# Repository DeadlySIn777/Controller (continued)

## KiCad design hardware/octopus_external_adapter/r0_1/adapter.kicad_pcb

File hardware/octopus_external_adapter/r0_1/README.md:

# Octopus external-driver adapter r0.1

**Engineering candidate for review and PCBWay DFM. Do not build or order from this revision yet.**

This is a separate single-axis StepStick adapter with a keyed four-pin output and a matching factory-made cable. The quote scenario is five assembled adapters and five cables: four axes plus one spare. Quantity and the proposed 500 mm cable length remain provisional.

**Confirmed delivery requirement: full turnkey assembly.** PCBWay is to fabricate the boards, source and fit all 12 components including every connector, manufacture and finish the matching cables, complete the agreed inspections/tests, and deliver depanelled, individually ESD-packed sets. The user receives finished assemblies requiring no soldering or crimping. Installation consists of plugging in each adapter/cable and securing the labelled leads in the driver terminals. This requirement does not change the unresolved compatibility or release gates.

The selected connector pair is a top-mounted JST `B4B-XH-A(LF)(SN)` shrouded header and cable `XHP-4` housing with female contacts. It provides the plug-in connection requested; the PCB header's protected contacts are male. Matching cables will be supplied, so the pictured cable is not assumed compatible.

| J3 cavity | Signal | Driver end |
| --- | --- | --- |
| 1 | +5 V common | Factory splice to PUL+, DIR+, ENA+ |
| 2 | PUL- | PUL- |
| 3 | DIR- | DIR- |
| 4 | ENA- | ENA- |

The candidate uses socket 5 V and an `SN74LVC3G06DCUR` triple open-drain inverter. **The VM contact and plated hole are physically absent**: J1 is an eight-pin header; J2 is a seven-pin header beginning one position lower, at GND. It is based on the **Octopus Pro V1.0 F429/F446** schematic, whose socket control signals are already buffered to 5 V. The user's exact board is unconfirmed. This is not a general 3.3 V-input adapter. The **CL57T V4.1** driver comes from the pasted discussion and also remains unconfirmed.

The **15.24 × 20.32 mm, two-layer** PCB is routed. Final native KiCad 10.0.4 ERC and DRC each report **zero errors and zero warnings**, with **zero unconnected items, zero schematic discrepancies and zero ignored checks**. The independent package check reconciles all **43 pin assignments, 12 components, 11 functional nets**, both header positions and nine SMT placements. Two filled ground copper layers connect the buffer and bypass returns. These are source/CAD results, not measured hardware performance; exact hashes and outstanding gates are in [verification.json](verification.json).

Start with the [actual 3D CAD render](adapter-3d.png), [assembly drawing](assembly-review.svg), [schematic PDF](adapter-schematic.pdf), or editable [PCB](adapter.kicad_pcb) and [schematic](adapter.kicad_sch). The [STEP assembly](adapter-assembly-review.step) supports mechanical review. The [PCBWay BOM](PCBWay_BOM_DRAFT.csv), [SMT placement file](PCBWay_CPL_DRAFT.csv), [quote draft](PCBWAY_QUOTE_DRAFT.md), [harness specification](HARNESS_SPEC.md), [cable pin map](cable_pinmap.csv), [cable BOM](cable_bom.csv), [test plan](FUNCTIONAL_TEST.md), and [sources](SOURCES.md) prepare the review package. All ordering files remain drafts. CPL origin is the lower-left board corner, X right/Y up, millimetres; THT assembly is specified separately.

Prototype order release still needs the exact host and driver identities, socket supply/logic confirmation, populated mechanical fit, driver-terminal/ferrule details, enable polarity and host timing review, and factory DFM/quotation. Quantity and cable length are provisional. The native source/PCB reconciliation is complete for this candidate. Before machine use, a first article requires loaded electrical, pulse, enable, power-sequence and actual-cable tests. The adapter makes no emergency-stop, STO or power-loss inhibition claim; alarm/brake/motor/encoder wiring remains separate.

Gerbers/drills have deliberately not been exported from this unreleased equipment profile. No external submission, quotation, purchase or physical test has occurred. The active twelve-channel controller motherboard, its routing, machine configurations and historical evidence were not edited for this adapter.

The reproducible sources are `build_schematic.py`, `build_pcb.py`, `route_candidate.py` and `package_review.py`. Use KiCad's bundled Python for the PCB scripts. `build_pcb.py` applies saved `routes.json`; changing placement or circuit requires rerouting and fresh native checks. After building, run native DRC with `--refill-zones --save-board --schematic-parity --severity-all`, and native ERC with `--severity-all`. Keep all release gates open until their evidence exists.

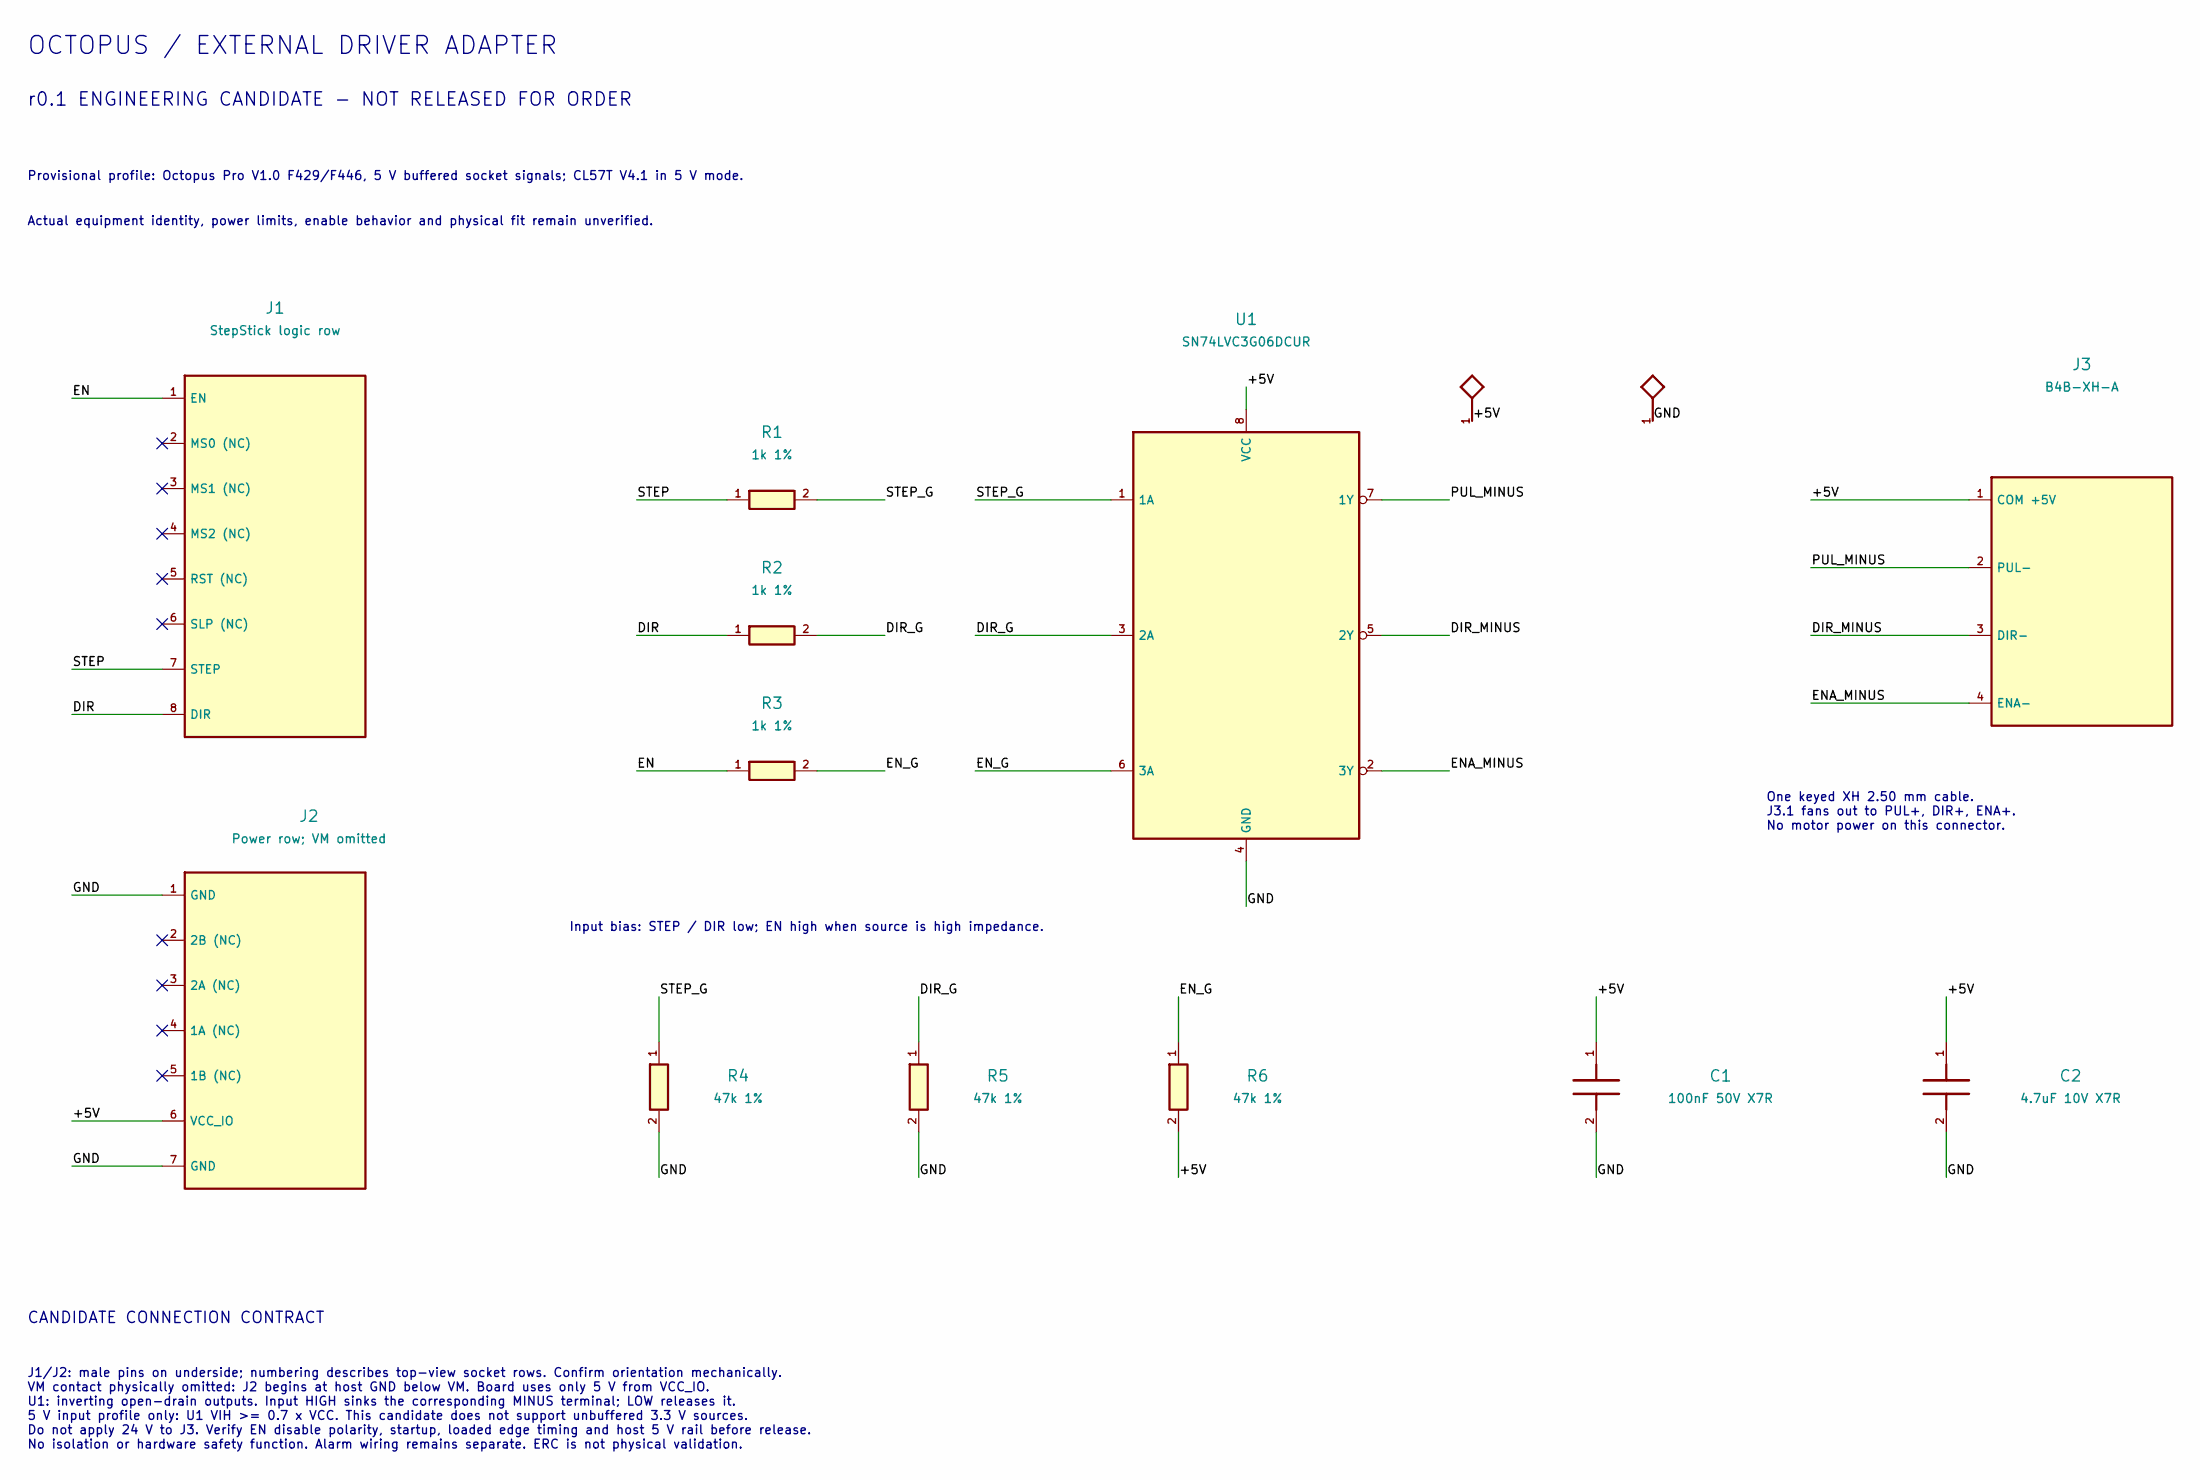
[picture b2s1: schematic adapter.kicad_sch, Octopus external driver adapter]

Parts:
C1: 100nF 50V X7R; C_0603_1608Metric; MPN CL10B104KB8NNNC
C2: 4.7uF 10V X7R; C_0805_2012Metric; MPN CC0805KKX7R6BB475
J1: StepStick logic row; Wurth_61300811121_1x08_P2.54mm; MPN 61300811121
J2: Power row; VM omitted; Wurth_61300711121_1x07_P2.54mm; MPN 61300711121
J3: B4B-XH-A; JST_XH_B4B-XH-A_1x04_P2.50mm_Vertical; MPN B4B-XH-A(LF)(SN)
R1, R2, R3: 1k 1%; R_0603_1608Metric; MPN RC0603FR-071KL
R4, R5, R6: 47k 1%; R_0603_1608Metric; MPN RC0603FR-0747KL
U1: SN74LVC3G06DCUR; VSSOP-8_2.3x2mm_P0.5mm; MPN SN74LVC3G06DCUR

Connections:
/+5V: C1.1, C2.1, J2.6 (VCC_IO), J3.1 (COM +5V), R6.2, U1.8 (VCC)
/DIR: J1.8 (DIR), R2.1
/DIR_G: R2.2, R5.1, U1.3 (2A)
/DIR_MINUS: J3.3 (DIR-), U1.5 (2Y)
/EN: J1.1 (EN), R3.1
/ENA_MINUS: J3.4 (ENA-), U1.2 (3Y)
/EN_G: R3.2, R6.1, U1.6 (3A)
/GND: C1.2, C2.2, J2.1 (GND), J2.7 (GND), R4.2, R5.2, U1.4 (GND)
/PUL_MINUS: J3.2 (PUL-), U1.7 (1Y)
/STEP: J1.7 (STEP), R1.1
/STEP_G: R1.2, R4.1, U1.1 (1A)

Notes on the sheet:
OCTOPUS / EXTERNAL DRIVER ADAPTER
r0.1 ENGINEERING CANDIDATE - NOT RELEASED FOR ORDER
Provisional profile: Octopus Pro V1.0 F429/F446, 5 V buffered socket signals; CL57T V4.1 in 5 V mode.
Actual equipment identity, power limits, enable behavior and physical fit remain unverified.
One keyed XH 2.50 mm cable. J3.1 fans out to PUL+, DIR+, ENA+. No motor power on this connector.
Input bias: STEP / DIR low; EN high when source is high impedance.
CANDIDATE CONNECTION CONTRACT
J1/J2: male pins on underside; numbering describes top-view socket rows. Confirm orientation mechanically. VM contact physically omitted: J2 begins at host GND below VM. Board uses only 5 V from VCC_IO. U1: inverting open-drain outputs. Input HIGH sinks the corresponding MINUS terminal; LOW release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

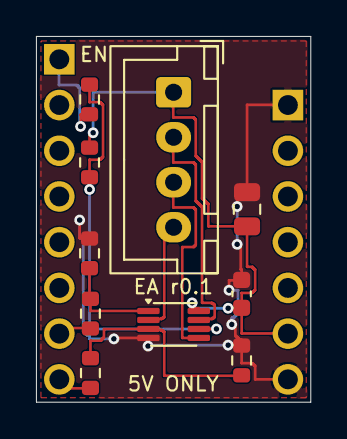
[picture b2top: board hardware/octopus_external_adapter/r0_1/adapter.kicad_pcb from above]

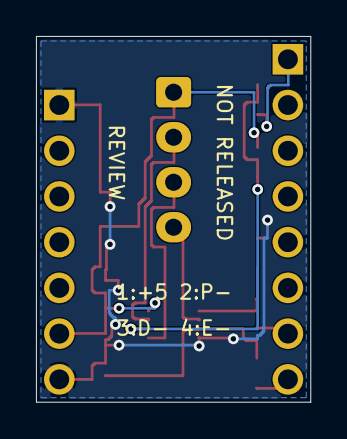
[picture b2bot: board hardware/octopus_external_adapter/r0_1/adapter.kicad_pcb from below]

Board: 2 copper layers, 15.2 x 20.3 mm, 12 parts (2 on the bottom side), 11 nets.

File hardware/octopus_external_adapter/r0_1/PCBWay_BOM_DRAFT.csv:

Designator,Quantity per board,Value,Manufacturer,MPN,Footprint,Assembly side,Type,Assembly note
J1,1,StepStick logic row,Wurth Elektronik,61300811121,Adapter:Wurth_61300811121_1x08_P2.54mm,Bottom,THT,Long mating pins point DOWN; VM position omitted on right row
J2,1,Power row; VM omitted,Wurth Elektronik,61300711121,Adapter:Wurth_61300711121_1x07_P2.54mm,Bottom,THT,Long mating pins point DOWN; VM position omitted on right row
J3,1,B4B-XH-A,JST,B4B-XH-A(LF)(SN),Connector_JST:JST_XH_B4B-XH-A_1x04_P2.50mm_Vertical,Top,THT,Cable entry UP
U1,1,SN74LVC3G06DCUR,Texas Instruments,SN74LVC3G06DCUR,Package_SO:VSSOP-8_2.3x2mm_P0.5mm,Top,SMT,
R1,1,1k 1%,Yageo,RC0603FR-071KL,Resistor_SMD:R_0603_1608Metric,Top,SMT,
R2,1,1k 1%,Yageo,RC0603FR-071KL,Resistor_SMD:R_0603_1608Metric,Top,SMT,
R3,1,1k 1%,Yageo,RC0603FR-071KL,Resistor_SMD:R_0603_1608Metric,Top,SMT,
R4,1,47k 1%,Yageo,RC0603FR-0747KL,Resistor_SMD:R_0603_1608Metric,Top,SMT,
R5,1,47k 1%,Yageo,RC0603FR-0747KL,Resistor_SMD:R_0603_1608Metric,Top,SMT,
R6,1,47k 1%,Yageo,RC0603FR-0747KL,Resistor_SMD:R_0603_1608Metric,Top,SMT,
C1,1,100nF 50V X7R,Samsung Electro-Mechanics,CL10B104KB8NNNC,Capacitor_SMD:C_0603_1608Metric,Top,SMT,
C2,1,4.7uF 10V X7R,Yageo,CC0805KKX7R6BB475,Capacitor_SMD:C_0805_2012Metric,Top,SMT,

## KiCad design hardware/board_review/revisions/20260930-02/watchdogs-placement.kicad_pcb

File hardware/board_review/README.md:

# Live board CAD review

**Current adopted board — Source26/ROOT104, published CAD30:** [Exact adoption](../../reports/motherboard-return-zoning-20261002/ROOT103-bypass-PROC-composed-r01/adoption.json) and the published board share SHA-256 `70b71c36778e49600b77f382cf84df81ef3ac6dce442cc0e576b494d307979cc`. There are **2,688 footprints, 11,807 track/via items, 1,544 zones/rule areas and 3,508 required joins remaining**. Native and independent uncapped connectivity agree: 633 fully joined and 1,101 incomplete multi-pad nets, zero orphan copper. Native regular DRC is **0 errors/0 warnings/no ignored checks**; Source26 ERC is **0 errors/70 unsuppressed warnings**, with [exact warning dispositions](../../reports/motherboard-erc-20261002/source26-exact-warning-disposition-r01/receipt.json). The 48 controlled additions preserve all prior copper, lands, poses and zone definitions. Actual saved/refilled removal of all 48 restores the baseline 3521 joins. Scoped proofs cover 120 bypass loops, 245 receiving returns and 188 Source-anchored filled resources. Source27 corrections remain staged; no Freerouting copper has been adopted.

[Fresh full r08](../../reports/pre-hardware-validation-20261002/full-bypass-PROC-seeded-IS2-r08/report.json) has **25 PASS, 9 BLOCKED, 1 physical NOT_RUN and 0 FAIL**, with **1,895 host and 238 native KiCad cases passing**, five Windows symlink skips and all 4,041 scoped source hashes unchanged. Fresh evidence includes 2,048 actual SPI seeded trials in eight fault classes, 18 reset/fault mechanical-model scenarios, the four-stage diagnostic IOL1 replay, the five-stage read-only IS2 CAP3 profile and eleven-stage stateful replay. These are compiled C/RTL and ideal-mechanics proofs, not complete HAL, target timing, electrical safety or measured hardware ratings.

[Characterization r06](../../reports/pre-hardware-characterization-20261002/characterization-register-r06/requirements-and-coverage.json) preserves all 15 subsystem, 22 fault and nine complete-machine requirements. No complete machine profile is yet validated. The original transport CAP3 gap and the bounded IS2 read-only implementation are distinct; the new profile deliberately remains unqualified and cannot authorize motion. Frozen CNC3 rate limits remain unchanged; the requested 2 MHz/channel target is not implemented/qualified. Complete IOL1 authority, record trust/provisioning, analog-chain convergence, vendor FPGA fit/timing and full-load operation remain open. The staged record-acquisition mapping exceeds the coarse T20 resource budget and is undergoing implementation optimization; HDL simulation alone does not prove capacity.

[Current native drill/land audit](../../reports/motherboard-pcb-integration-20261002/ROOT103-bypass-PROC-full-drill-SMD-r01/receipt.json) finds **274 drilled vias intersecting 277 same-net paste SMD lands**, zero foreign-net intersections and no added overlap in ROOT104. This lower bound excludes tangency and registration margins. Layout correction or exact qualified filled/capped fabrication and assembly is still required; tenting and clean ordinary DRC do not close it. The **460×340 mm, six-layer, 1.6 mm** stackup remains provisional. Final routing, power distribution, complete 20 ms inhibit, mechanics, manufacturing outputs and physical validation are unfinished. **Manufacturing readiness remains false.**

[Unchanged Source26 partial BOM v11](../../reports/motherboard-cost-20260930/source-r26-2688-complete-cost-v11/README.md) has known-priced consumed parts at 1/10/100 units of **US$1,091.51/$877.37/$796.51**; 105 exact MPNs are priced and 185 MPNs/720 fitted pieces remain unpriced. Plug-in modules, screens, fabrication, assembly, programming/test, enclosure and packaging remain separate unknowns. This is not a complete product cost or PCBWay quote.

30 September 2026. User-requested physical design view, backed by editable native KiCad placement files. Open `http://127.0.0.1:8788/index.html` in the Codex right panel while the local review server runs. It serves only this review folder on loopback; it does not connect to a machine or require an online service.

The viewer offers top CAD, native KiCad 3D renders, pan/zoom, component search, source part and pin-net inspection, highlighted changes/review focus and a revision selector. It polls the published manifest every three seconds. A newly published revision updates the latest view; an intentionally selected old revision stays visible until the user selects the update. The server does **not** regenerate CAD when schematics change: the engineering update procedure below publishes that change.

## Current published revision: 20261002-30; working PCB: Source26/ROOT104

[Native KiCad project](revisions/20261002-30/motherboard-native-candidate.kicad_pcb), [native render](revisions/20261002-30/motherboard-3d.png) and [publication proof](revisions/20261002-30/publication.json) share the adopted board bytes. Publication reruns native DRC and uncapped connectivity; the 499-item native display cap is not the 3508 required-join total. The package retains92 checked footprint patterns and both local model references. This is an incomplete editable design, not a fabrication package.

## Historical published revision: 20260930-21

Published native CAD **20260930-21** contains the separate frozen **880-footprint / 878 fitted** snapshot. It preserves the original 327 footprints, **2,088 track/via items and five filled zones**. Independent uncapped connectivity finds **1,600 missing joins**. Native DRC reports **zero regular violations, no ignored checks and 499 capped unconnected items**; routing fails. The **460 × 340 mm, six-layer, 1.6 mm** outline remains provisional; existing planes cover the retained core rather than the whole motherboard.

The reconciled electrical source has **1585 physical footprints: 1557 purchased fitted parts, 26 bare PCB test pads and two DNP footprints**, across eighteen source blocks. It contains all twelve motor interfaces, four ABZ receiving paths, 24 DI, 16 smart DO, power-health, actual I/O controllers, protected power entry, probe/pendant supplies, purchased-module compute/ESP sockets and process control with its fourth actual acquisition controller. Native integrated ERC is **zero errors, 72 warnings, no ignored checks** (70 isolated-pin labels and two ground-name warnings). Independent native fitted pin/MPN/footprint and exact original-pin/topology checks pass. The 23 root integration, 26 FPGA allocation, 33 ACC, 35 process and 10 ESP focused tests pass; these do not prove firmware execution or physical behavior.

The additional source parts are being populated onto the existing PCB without discarding its routed copper. Storage and compute raw peripherals, analog/comms, status indicators, actual field terminals, complete power/return routing and mechanical/thermal reconciliation remain engineering work. Logic-rail startup load and monitor-window corrections are under review. The 20 ms inhibit requirement, partial-power behavior, target firmware, vendor FPGA package fit/timing and physical/EMC/thermal qualification remain unproved. Gerbers, drills, final assembly CPL/drawings and a final stackup have not been released; manufacturing_ready remains false. Original six-joint/two-encoder runtime results remain historical baseline evidence; twelve fitted interfaces are not twelve proven coordinated axes.

[Native PCB](revisions/20260930-21/motherboard-populated-candidate.kicad_pcb), [publication receipt](revisions/20260930-21/publication.json), [uncapped connectivity](revisions/20260930-21/publication-connectivity/review.json).

## Historical initial CAD scope: revisions 01â€“03

The following table and observations describe the initial placement studies, not the current integrated MC. Their original native files, source review and DRC records remain historical evidence. Later integration and partial routing are recorded above.

| Study | Current physical review content | Important boundary |
|---|---|---|
| MC motion card | 70 FPGA-core component candidates, 411 pads, 214 represented nets | Proposed IS-1 220 Ã— 100 mm card envelope; not a complete motion card |
| Dual-watchdog circuit | 22 component candidates, 68 pads, 18 represented nets | Separate unintegrated circuit on a provisional 60 Ã— 45 mm review canvas; not an adopted product module |

MC imports 68 footprint assignments from the electrical source and makes **two placement-only** assignments for U1 and Y1. Their pad numbering/body geometry was independently checked in [the source review](../../reports/board-cad-20260930/SOURCE_REVIEW.md); their source schematic/BOM assignments remain unchanged. Logical boundary symbols are recorded but have not been turned into fabricated connectors. All fitted native-board pad nets round-trip against the source netlists. No copper tracks, planes, vias, stackup qualification, final connector placement, mounting holes or fabrication exports exist here. The study's 1.6 mm thickness is an explicit assumption.

The MC's card-local power, identity, Ioff buffering, final permission/self-test circuits and connector allocation remain incomplete. The watchdogs are not integrated into MC; their known startup and conditioning issues remain open. Other controller cards and the passive wiring base have no new board layout in this delivery. The historical six/two runtime and required eight/twelve product scope remain distinct from CAD placement evidence.

The top view shows every imported footprint. Installed 3D models cover **68/70 MC parts** and **20/22 watchdog parts**. The native 3D render omits the body models for MC U1/Y1 and watchdog U1/U2; their actual pads remain present. The viewer states these omissions explicitly rather than inventing package heights.

Native DRC ran on revision `20260930-03`: no other reported rule violations, but **197 MC and 50 watchdog unconnected items** remain. This is an **unrouted DRC result, not a DRC pass or manufacturing approval**. Schematic parity, board-level electrical completeness and physical measurements are not established by this review. Raw native reports and independent placement review are under `reports/board-cad-20260930/`.

The [independent native placement QA](../../reports/board-cad-20260930/PLACEMENT_QA.md) checks source pin sets, pad nets, manifest geometry/hashes and conservative pad/component/courtyard envelopes. It found no intersecting or outside checked envelopes. Watchdog U1/U2 have **no source courtyard shapes**, so their courtyard check remains incomplete. The native study files use KiCad's default two copper layers; that is a review-file default, **not** the selected production stackup.

## Updating the view as engineering changes

For a routed candidate, preserve the prior published native copper and compare both source-pin/net parity and actual physical connectivity before publishing. `tools/publish_routed_board_review.py` publishes a reviewed routed board under a new unique revision, with optional staged placement inputs, fresh native DRC/render and a publication receipt. The builder example below remains the placement-study workflow; rebuilding placement alone is not a substitute for preserving and verifying existing routed geometry. Do not report the capped native unconnected list as an uncapped routing total. Keep the independent all-net inventory synchronized with the actual published board hash.

1. Update the electrical circuit through its existing generator/review workflow, preserving the user sources and machine configurations.
2. Update `placement.json` with reviewed positions, allocations or placement-only footprint candidates. Keep physical quantities and omitted circuitry explicit. The native studies are separate from any future production routed board, and archived native files remain editable in KiCad.
3. Build a **new unique revision** with KiCad's bundled Python. The builder refuses to overwrite a revision, imports source pad nets, verifies native save/reload and source integrity, compares component geometry/content with the preceding published revision and atomically publishes `board-view.json`. Differences and unchanged engineering focus receive distinct reasons.
4. Render both new native boards and save fresh DRC reports. Review geometry/footprint assignments and record remaining violations. The viewer updates in the same browser panel; previous revisions stay selectable.

Example from the project directory, replacing the revision and label with the actual new increment:

```powershell
& 'C:/Program Files/KiCad/10.0/bin/python.exe' tools/build_board_review.py --revision 20261001-01 --label 'Describe the actual engineering change'
& 'C:/Program Files/KiCad/10.0/bin/kicad-cli.exe' pcb render --output hardware/board_review/revisions/20261001-01/motion-card-3d.png --width 1600 --height 900 --background opaque --rotate '-35,0,0' --zoom 1.5 hardware/board_review/revisions/20261001-01/motion-card-placement.kicad_pcb
& 'C:/Program Files/KiCad/10.0/bin/kicad-cli.exe' pcb render --output hardware/board_review/revisions/20261001-01/watchdogs-3d.png --width 1200 --height 900 --background opaque --rotate '-35,0,0' --zoom 1.5 hardware/board_review/revisions/20261001-01/watchdogs-placement.kicad_pcb
```

Restart the local viewer server after a reboot if needed:

```powershell
python -X utf8 tools/serve_board_review.py --port 8788
```

Published history: `20260930-01` initial placement; `20260930-02` readable native labels/custom-library portability; `20260930-03` change-comparison metadata; `20260930-04` integrated 203-part MC; `20260930-05` placement/local-power geometry review; `20260930-06` partial copper; `20260930-10` integrated 327-part MC partial copper; `20260930-12` historical r0.3/active-cap partial routing; `20260930-14` current r0.4, exact oscillator source assignment, custom courtyards, tube-packaged supervisors and strict native review retaining all 673 copper items. The manifest's revision selector is the published-history authority; unpublished staging directories are separate evidence. The interrupted `20260930-01-build-incomplete` directory remains excluded from the viewer. No listed revision establishes a finished controller or fabrication approval.

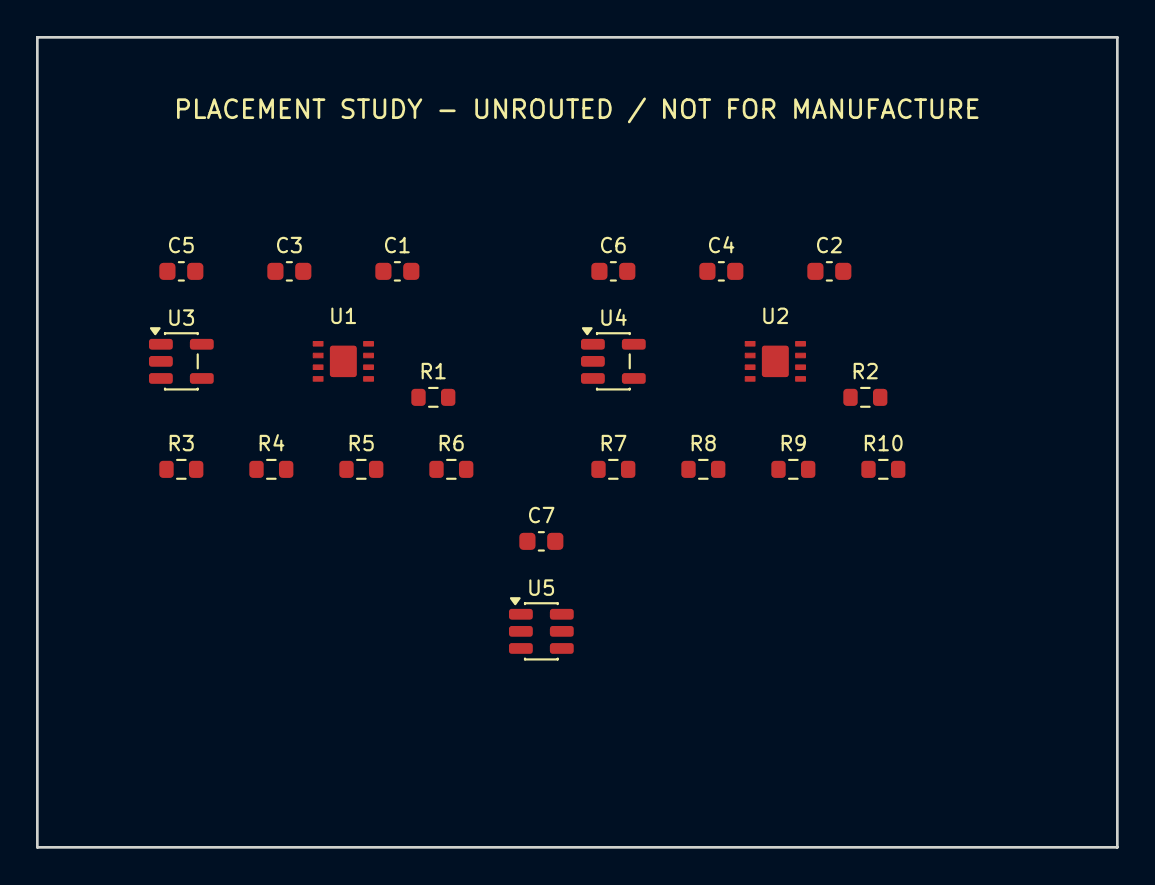
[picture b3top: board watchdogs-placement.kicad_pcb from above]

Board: 2 copper layers, 60.0 x 45.0 mm, 22 parts (0 on the bottom side), 14 nets, no tracks yet.

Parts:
C1, C2: CL10C332JB8NNNC; C_0603_1608Metric
C3, C4, C5, C6, C7: GRM188R71E104KA01D; C_0603_1608Metric
R1, R2: CRCW060310K0FKEA; R_0603_1608Metric
R3, R4, R5, R6, R7, R8, R9, R10: CRCW0603100KFKEA; R_0603_1608Metric
U1, U2: TPS3851G18SDRBT; TPS3851_DRB8
U3, U4: SN74LVC1G34DBVR; SOT-23-5
U5: SN74LVC2G17DBVR; SOT-23-6

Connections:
/FPGA_MOTION_REQUEST: R3.1, U1.5
/FPGA_OUTPUT_REQUEST: R4.1, U2.5
/FPGA_PROGRESS_M: R5.1, U3.2
/FPGA_PROGRESS_O: R7.1, U4.2
/IO_3V3: C3.1, C4.1, C5.1, C6.1, C7.1, R1.1, R2.1, U1.1, U2.1, U3.5, U4.5, U5.5
/LOGIC_GND: C1.2, C2.2, C3.2, C4.2, C5.2, C6.2, C7.2, R3.2, R4.2, R5.2, R6.2, R7.2, R8.2, R9.2, R10.2, U1.4, U1.9, U2.4, U2.9, U3.3, U4.3, U5.2
/WD_M_CWD: C1.1, U1.2
/WD_M_HEALTH_RAW: R1.2, U1.7, U1.8, U5.1
/WD_M_OK: R9.1, U5.6
/WD_M_WDI_BUF: R6.1, U1.6, U3.4
/WD_O_CWD: C2.1, U2.2
/WD_O_HEALTH_RAW: R2.2, U2.7, U2.8, U5.3
/WD_O_OK: R10.1, U5.4
/WD_O_WDI_BUF: R8.1, U2.6, U4.4

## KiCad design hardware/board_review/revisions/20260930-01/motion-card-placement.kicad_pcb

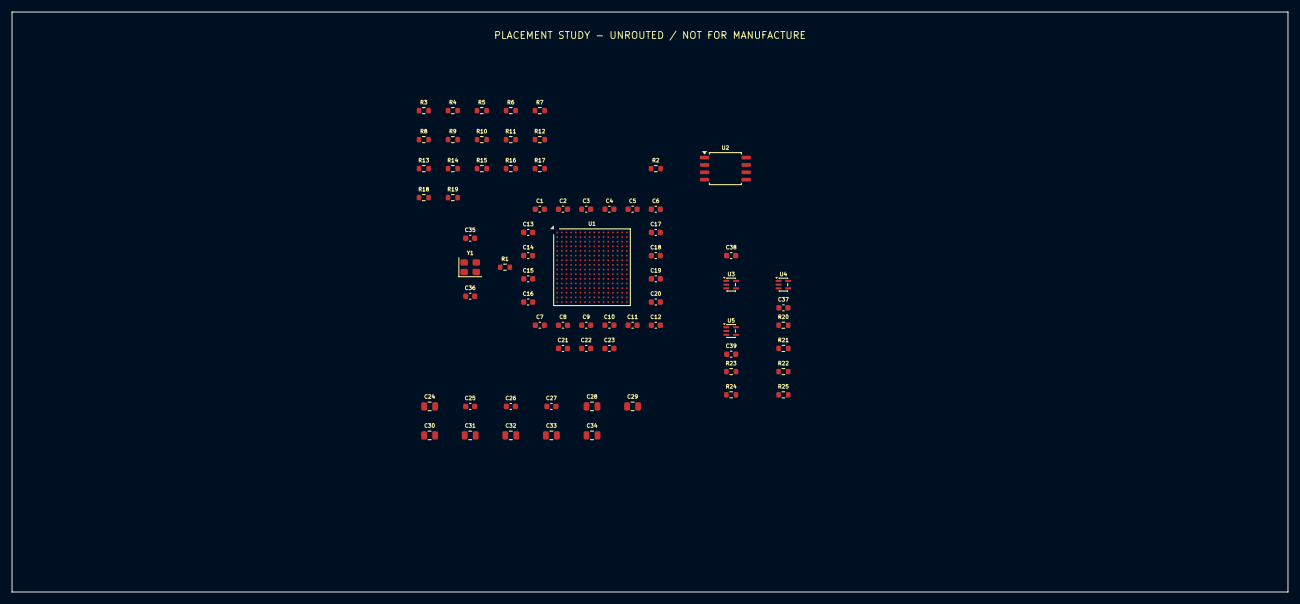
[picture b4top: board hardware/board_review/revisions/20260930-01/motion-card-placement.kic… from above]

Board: 2 copper layers, 220.0 x 100.0 mm, 70 parts (0 on the bottom side), 33 nets, no tracks yet.

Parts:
C1, C2, C3, C4, C5, C6, C7, C8, C9, C10, C11, C12, C13, C14, C15, C16, C17, C18, C19, C20, C21, C22, C23, C35, C38: 885012206046; C_0603_1608Metric
C24, C28, C29, C30, C31, C32, C33, C34: 885012207053; C_0805_2012Metric
C25, C26, C27, C36, C39: 885012206052; C_0603_1608Metric
C37: 885012206040; C_0603_1608Metric
R1, R2: CRCW060333R0FKEA; R_0603_1608Metric
R3, R4, R5, R6, R7, R8, R9, R10, R11, R12, R13, R14, R15, R16, R17, R18, R19, R22, R23, R24, R25: CRCW060310K0FKEA; R_0603_1608Metric
R20: CRCW060347K0FKEA; R_0603_1608Metric
R21: CRCW06031K00FKEA; R_0603_1608Metric
U1: T20F256I4; TFBGA-256_13x13mm_Layout16x16_P0.8mm
U2: W25Q32JVSSIQ; SOIC-8_5.3x5.3mm_P1.27mm
U3, U5: SN74LVC1G08DCKR; SOT-353_SC-70-5
U4: 74LVC1G17GW; SOT-353_SC-70-5
Y1: ASE-50.000MHZ-L-C-T; Oscillator_SMD_Abracon_ASE-4Pin_3.2x2.5mm

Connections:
/CORE_1V2: C1.1, C2.1, C3.1, C4.1, C5.1, C6.1, C7.1, C8.1, C9.1, C24.1, C25.1, C26.1, C27.1, U1.E9, U1.F7, U1.F8, U1.F9, U1.G11, U1.J6, U1.J7, U1.K9, U1.K11
/FPGA_CDONE: R3.2, R22.1, U1.R1
/FPGA_CFG_CBSEL0: R18.1, U1.C7
/FPGA_CFG_CBSEL1: R19.1, U1.D7
/FPGA_CFG_CBUS0: R9.2, U1.K13
/FPGA_CFG_CBUS1: R8.2, U1.L14
/FPGA_CFG_CBUS2: R7.2, U1.R16
/FPGA_CFG_CSI: R4.2, U1.N3
/FPGA_CFG_NSTATUS: R17.2, U1.B8
/FPGA_CFG_TEST_N: R5.2, U1.L12
/FPGA_CLK_50M: R1.2, U1.H3
/FPGA_CLK_SOURCE: R1.1, Y1.3
/FPGA_ENDPOINT_READY: R23.1, U1.C4
/FPGA_FLASH_CCK: R2.2, U2.6
/FPGA_FLASH_CCK_SOURCE: R2.1, U1.M3
/FPGA_FLASH_CS_N: R6.2, U1.P3, U2.1
/FPGA_FLASH_IO2: R14.2, U2.3
/FPGA_FLASH_IO3: R15.2, U2.7
/FPGA_FLASH_MISO: U1.N1, U2.2
/FPGA_FLASH_MOSI: U1.L3, U2.5
/FPGA_JTAG_TCK: R10.2, U1.M2
/FPGA_JTAG_TDI: R11.2, U1.K5
/FPGA_JTAG_TDO: R13.2, U1.L5
/FPGA_JTAG_TMS: R12.2, U1.M1
/FPGA_LOCAL_RESET_N: R20.2, R21.1, U1.P1, U3.4
/FPGA_MOTION_REQUEST: R24.1, U1.B3
/FPGA_PROGRESS_WDI: R25.1, U1.E4
/FPGA_SERVICE_RUN_N: R16.2, U3.2, U5.2
/FPGA_USER_RESET_DELAYED: U4.4, U5.1
/FPGA_USER_RESET_N: U1.D5, U5.4
/FPGA_USER_RESET_RC: C39.1, R22.2, U4.2
/IO_3V3: C10.1, C11.1, C12.1, C13.1, C14.1, C15.1, C16.1, C17.1, C18.1, C19.1, C20.1, C21.1, C22.1, C23.1, C28.1, C29.1, C30.1, C31.1, C32.1, C33.1, C34.1, C35.1, C36.1, C37.1, C38.1, R3.1, R4.1, R5.1, R6.1, R7.1, R8.1, R9.1, R10.1, R11.1, R12.1, R13.1, R14.1, R15.1, R16.1, R17.1, R20.1, U1.E10, U1.F6, U1.F10, U1.F11, U1.G6, U1.H6, U1.H7, U1.J10, U1.J11, U1.K6, U1.L6, U1.L7, U1.L10, U1.L11, U2.8, U3.5, U4.5, U5.5, Y1.1, Y1.4
/LOGIC_GND: C1.2, C2.2, C3.2, C4.2, C5.2, C6.2, C7.2, C8.2, C9.2, C10.2, C11.2, C12.2, C13.2, C14.2, C15.2, C16.2, C17.2, C18.2, C19.2, C20.2, C21.2, C22.2, C23.2, C24.2, C25.2, C26.2, C27.2, C28.2, C29.2, C30.2, C31.2, C32.2, C33.2, C34.2, C35.2, C36.2, C37.2, C38.2, C39.2, R18.2, R19.2, R21.2, R23.2, R24.2, R25.2, U1.A1, U1.A5, U1.A12, U1.A16, U1.D2, U1.D15, U1.G7, U1.G8, U1.G9, U1.G10, U1.H8, U1.H9, U1.H10, U1.H11, U1.J1, U1.J8, U1.J9, U1.J16, U1.K7, U1.K8, U1.K10, U1.L8, U1.L9, U1.N2, U1.N15, U1.R7, U1.R10, U1.T1, U1.T4, U1.T13, U1.T16, U2.4, U3.3, U4.3, U5.3, Y1.2

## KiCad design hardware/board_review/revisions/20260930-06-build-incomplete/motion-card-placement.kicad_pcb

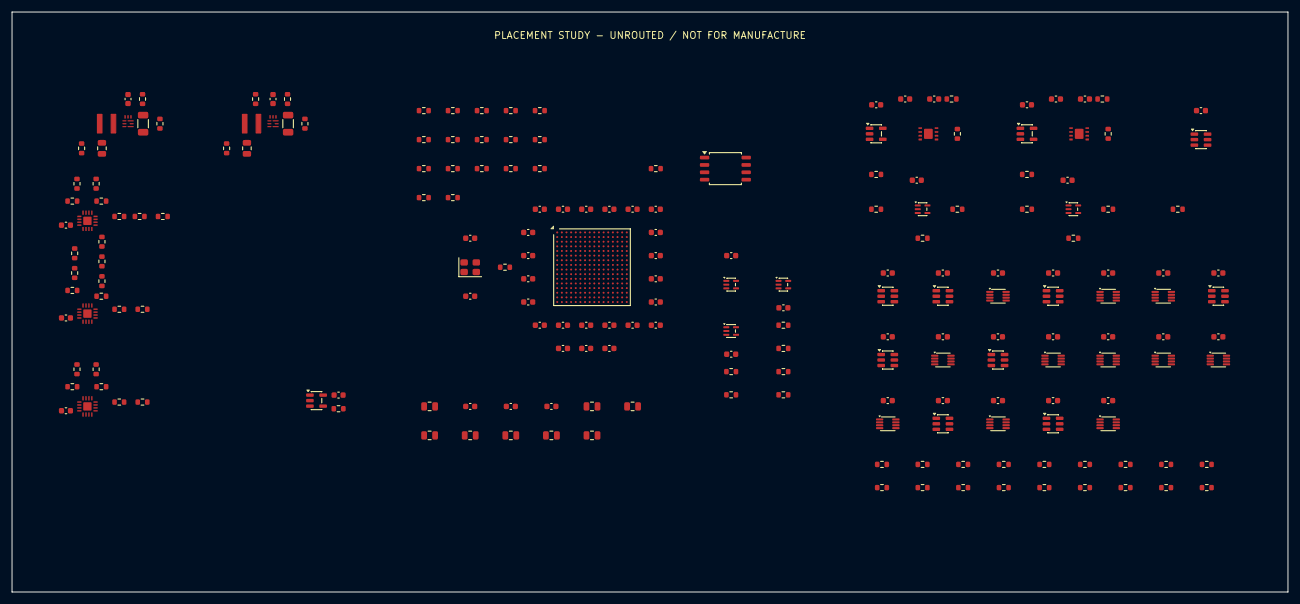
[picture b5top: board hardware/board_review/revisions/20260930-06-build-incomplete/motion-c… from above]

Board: 6 copper layers, 220.0 x 100.0 mm, 203 parts (0 on the bottom side), 103 nets, no tracks yet.

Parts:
C1001, C1002, C1003, C1004, C1005, C1006, C1007, C1008, C1009, C1010, C1011, C1012, C1013, C1014, C1015, C1016, C1017, C1018, C1019, C1020, C1021, C1022, C1023, C1035, C1038: 885012206046; C_0603_1608Metric
C1024, C1028, C1029, C1030, C1031, C1032, C1033, C1034: 885012207053; C_0805_2012Metric
C1025, C1026, C1027, C1036, C1039: 885012206052; C_0603_1608Metric
C1037: 885012206040; C_0603_1608Metric
C2001, C2004: C3216X7R1E106K160AB; C_1206_3216Metric
C2002, C2005: C2012X7S1A226M125AC; C_0805_2012Metric
C2003, C2006: GRM1885C1H682JA01D; C_0603_1608Metric
C2007, C2008, C2009, C2010, C3003, C3004, C3005, C3006, C3007, C3008, C3009, C4001, C4002, C4003, C4004, C4005, C4006, C4007, C4008, C4009, C4010, C4011, C4012, C4013, C4014, C4015, C4016, C4017, C4018, C4019: GRM188R71E104KA01D; C_0603_1608Metric
C3001, C3002: CL10C332JB8NNNC; C_0603_1608Metric
L2001: XGL4020-222MEC; XGL4020
L2002: XGL4020-102MEC; XGL4020
R1001, R1002: CRCW060333R0FKEA; R_0603_1608Metric
R1003, R1004, R1005, R1006, R1007, R1008, R1009, R1010, R1011, R1012, R1013, R1014, R1015, R1016, R1017, R1018, R1019, R1022, R1023, R1024, R1025, R2002, R2006, R2103, R2105, R3001, R3002, R4008, R4009, R4010, R4011, R4012, R4013, R4014, R4015, R4016, R4017, R4018: CRCW060310K0FKEA; R_0603_1608Metric
R1020, R2106: CRCW060347K0FKEA; R_0603_1608Metric
R1021: CRCW06031K00FKEA; R_0603_1608Metric
R2001: CRCW060376K8FKEA; R_0603_1608Metric
R2003, R2007, R3006, R3008, R3009, R3010, R3011, R3012: CRCW0603100KFKEA; R_0603_1608Metric
R2005: CRCW060332K4FKEA; R_0603_1608Metric
R2008: CRCW0603301KFKEA; R_0603_1608Metric
R2021: PLT0603Z8792LST1; R_0603_1608Metric
R2027, R2035, R2067, R2075: PLT0603Z1002LST1; R_0603_1608Metric
R2029: PLT0603Z9212LST1; R_0603_1608Metric
R2041: PLT0603Z1071LST1; R_0603_1608Metric
R2042: PLT0603Z2610LST1; R_0603_1608Metric
R2047, R2055: PLT0603Z1001LST1; R_0603_1608Metric
R2049: PLT0603Z1151LST1; R_0603_1608Metric
R2050: PLT0603Z3160LST1; R_0603_1608Metric
R2051: CRCW06034R02FKEA; R_0603_1608Metric
R2061: PLT0603Z5452LST1; R_0603_1608Metric
R2069: PLT0603Z5752LST1; R_0603_1608Metric
R2101, R2102: CRCW06033K30FKEA; R_0603_1608Metric
R2104: CRCW06036K80FKEA; R_0603_1608Metric
R2107: CRCW0603470KFKEA; R_0603_1608Metric
R2108, R3003, R3004, R3005, R3007, R3013, R4001, R4002, R4003, R4004, R4005, R4006, R4007: CRCW06034K70FKEA; R_0603_1608Metric
U1001: T20F256I4; T20F256_Efinix_NSMD
U1002: W25Q32JVSSIQ; SOIC-8_5.3x5.3mm_P1.27mm
U1003, U1005, U3006, U3007: SN74LVC1G08DCKR; SOT-353_SC-70-5
U1004: 74LVC1G17GW; SOT-353_SC-70-5
U2001, U2002: TPS62901RPJR; TPS62901_RPJ9
U2003, U2004, U2005: LTC2962HUD#TRPBF; LTC2962_UD16
U2006: SN74LVC1G17DBVR; SOT-23-5
U3001, U3002: TPS3851G18SDRBT; TPS3851_DRB8
U3003, U3004: SN74LVC1G34DBVR; SOT-23-5
U3005: SN74LVC2G17DBVR; SOT-23-6
U4001, U4002, U4004, U4007, U4008, U4010: SN74LVC1G11DBVR; SOT-23-6
U4003, U4009, U4019: SN74LVC2G08DCUR; VSSOP-8_2.3x2mm_P0.5mm
U4005, U4006, U4011, U4012, U4013, U4014, U4015: SN74LVC2G74DCUR; VSSOP-8_2.3x2mm_P0.5mm
U4016, U4018: SN74LVC2G04DBVR; SOT-23-6
U4017: SN74LVC2G32DCUR; VSSOP-8_2.3x2mm_P0.5mm
Y1001: ASE-50.000MHZ-L-C-T; Oscillator_SMD_Abracon_ASE-4Pin_3.2x2.5mm

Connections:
/CORE_1V2: C1001.1, C1002.1, C1003.1, C1004.1, C1005.1, C1006.1, C1007.1, C1008.1, C1009.1, C1024.1, C1025.1, C1026.1, C1027.1, C2002.1, L2001.2, R2003.1, R2041.1, R2049.1, U1001.E9, U1001.F7, U1001.F8, U1001.F9, U1001.G11, U1001.J6, U1001.J7, U1001.K9, U1001.K11, U2001.3
/FPGA_CRESET_N: R2108.1, R4008.1, U1003.1, U2006.4, U4001.1, U4019.1, U4019.5
/FPGA_ENDPOINT_READY: R1023.1, R4001.1, U1001.C4, U4003.6, U4004.6
/FPGA_MOTION_REQUEST: R1024.1, R3003.1, U1001.B3, U3006.1, U4005.1, U4007.3
/FPGA_OUTPUT_REQUEST: R3004.1, U3007.1, U4006.1, U4008.3
/FPGA_PROGRESS_M: R1025.1, R3005.1, U1001.E4, U3003.2
/FPGA_USER_RESET_N: R3013.1, R4009.1, U1001.D5, U1005.4, U3006.2, U3007.2, U4001.3
/IO_3V3: C1010.1, C1011.1, C1012.1, C1013.1, C1014.1, C1015.1, C1016.1, C1017.1, C1018.1, C1019.1, C1020.1, C1021.1, C1022.1, C1023.1, C1028.1, C1029.1, C1030.1, C1031.1, C1032.1, C1033.1, C1034.1, C1035.1, C1036.1, C1037.1, C1038.1, C2005.1, C2010.1, C3003.1, C3004.1, C3005.1, C3006.1, C3007.1, C3008.1, C3009.1, C4001.1, C4002.1, C4003.1, C4004.1, C4005.1, C4006.1, C4007.1, C4008.1, C4009.1, C4010.1, C4011.1, C4012.1, C4013.1, C4014.1, C4015.1, C4016.1, C4017.1, C4018.1, C4019.1, L2002.2, R1003.1, R1004.1, R1005.1, R1006.1, R1007.1, R1008.1, R1009.1, R1010.1, R1011.1, R1012.1, R1013.1, R1014.1, R1015.1, R1016.1, R1017.1, R1020.1, R2007.1, R2061.1, R2069.1, R3001.1, R3002.1, U1001.E10, U1001.F6, U1001.F10, U1001.F11, U1001.G6, U1001.H6, U1001.H7, U1001.J10, U1001.J11, U1001.K6, U1001.L6, U1001.L7, U1001.L10, U1001.L11, U1002.8, U1003.5, U1004.5, U1005.5, U2002.3, U2006.5, U3001.1, U3002.1, U3003.5, U3004.5, U3005.5, U3006.5, U3007.5, U4001.5, U4002.5, U4003.8, U4004.5, U4005.2, U4005.7, U4005.8, U4006.2, U4006.7, U4006.8, U4007.5, U4008.5, U4009.8, U4010.5, U4011.2, U4011.7, U4011.8, U4012.2, U4012.7, U4012.8, U4013.2, U4013.7, U4013.8, U4014.7, U4014.8, U4015.7, U4015.8, U4016.5, U4017.8, U4018.5, U4019.8, Y1001.1, Y1001.4
/LOGIC_GND: C1001.2, C1002.2, C1003.2, C1004.2, C1005.2, C1006.2, C1007.2, C1008.2, C1009.2, C1010.2, C1011.2, C1012.2, C1013.2, C1014.2, C1015.2, C1016.2, C1017.2, C1018.2, C1019.2, C1020.2, C1021.2, C1022.2, C1023.2, C1024.2, C1025.2, C1026.2, C1027.2, C1028.2, C1029.2, C1030.2, C1031.2, C1032.2, C1033.2, C1034.2, C1035.2, C1036.2, C1037.2, C1038.2, C1039.2, C2001.2, C2002.2, C2003.2, C2004.2, C2005.2, C2006.2, C2007.2, C2008.2, C2009.2, C2010.2, C3001.2, C3002.2, C3003.2, C3004.2, C3005.2, C3006.2, C3007.2, C3008.2, C3009.2, C4001.2, C4002.2, C4003.2, C4004.2, C4005.2, C4006.2, C4007.2, C4008.2, C4009.2, C4010.2, C4011.2, C4012.2, C4013.2, C4014.2, C4015.2, C4016.2, C4017.2, C4018.2, C4019.2, R1018.2, R1019.2, R1021.2, R1023.2, R1024.2, R1025.2, R2001.2, R2002.2, R2003.2, R2005.2, R2006.2, R2007.2, R2008.2, R2027.2, R2035.2, R2047.2, R2055.2, R2067.2, R2075.2, R2103.2, R2105.2, R2107.2, R2108.2, R3003.2, R3004.2, R3005.2, R3006.2, R3007.2, R3008.2, R3009.2, R3010.2, R3011.2, R3012.2, R3013.2, R4001.2, R4002.2, R4003.2, R4004.2, R4005.2, R4006.2, R4007.2, R4008.2, R4009.2, R4010.2, R4011.2, R4012.2, R4013.2, R4014.2, R4015.2, R4016.2, R4017.2, R4018.2, U1001.A1, U1001.A5, U1001.A12, U1001.A16, U1001.D2, U1001.D15, U1001.G7, U1001.G8, U1001.G9, U1001.G10, U1001.H8, U1001.H9, U1001.H10, U1001.H11, U1001.J1, U1001.J8, U1001.J9, U1001.J16, U1001.K7, U1001.K8, U1001.K10, U1001.L8, U1001.L9, U1001.N2, U1001.N15, U1001.R7, U1001.R10, U1001.T1, U1001.T4, U1001.T13, U1001.T16, U1002.4, U1003.3, U1004.3, U1005.3, U2001.4, U2001.9, U2002.4, U2003.3, U2003.7, U2003.11, U2003.17, U2004.3, U2004.7, U2004.11, U2004.17, U2005.3, U2005.7, U2005.11, U2005.17, U2006.3, U3001.4, U3001.9, U3002.4, U3002.9, U3003.3, U3004.3, U3005.2, U3006.3, U3007.3, U4001.2, U4002.2, U4003.4, U4004.2, U4005.4, U4006.4, U4007.2, U4008.2, U4009.4, U4010.2, U4011.4, U4012.4, U4013.4, U4014.4, U4015.4, U4016.2, U4017.4, U4018.2, U4019.4, Y1001.2
/RAW_INHIBIT_N: U1001.A2, U4003.5, U4003.7, U4007.6
/TX_PERMIT: R4015.1, U1001.E6, U4007.4, U4009.5, U4010.1, U4011.6
/WD_M_OK: R3009.1, U3005.6, U4003.2, U4016.1
/WD_M_SET1_BUF: R3011.1, U3001.5, U3006.4, U4017.2
/WD_O_OK: R3010.1, U3005.4, U4004.3, U4009.2, U4016.3
/WD_O_SET1_BUF: R3012.1, U3002.5, U3007.4, U4017.6
/fpga_core/FPGA_CDONE: R1003.2, R1022.1, U1001.R1
/fpga_core/FPGA_CFG_CBSEL0: R1018.1, U1001.C7
/fpga_core/FPGA_CFG_CBSEL1: R1019.1, U1001.D7
/fpga_core/FPGA_CFG_CBUS0: R1009.2, U1001.K13
/fpga_core/FPGA_CFG_CBUS1: R1008.2, U1001.L14
/fpga_core/FPGA_CFG_CBUS2: R1007.2, U1001.R16
/fpga_core/FPGA_CFG_CSI: R1004.2, U1001.N3
/fpga_core/FPGA_CFG_NSTATUS: R1017.2, U1001.B8
/fpga_core/FPGA_CFG_TEST_N: R1005.2, U1001.L12
/fpga_core/FPGA_CLK_50M: R1001.2, U1001.H3
/fpga_core/FPGA_CLK_SOURCE: R1001.1, Y1001.3
/fpga_core/FPGA_FLASH_CCK: R1002.2, U1002.6
/fpga_core/FPGA_FLASH_CCK_SOURCE: R1002.1, U1001.M3
/fpga_core/FPGA_FLASH_CS_N: R1006.2, U1001.P3, U1002.1
/fpga_core/FPGA_FLASH_IO2: R1014.2, U1002.3
/fpga_core/FPGA_FLASH_IO3: R1015.2, U1002.7
/fpga_core/FPGA_FLASH_MISO: U1001.N1, U1002.2
/fpga_core/FPGA_FLASH_MOSI: U1001.L3, U1002.5
/fpga_core/FPGA_JTAG_TCK: R1010.2, U1001.M2
/fpga_core/FPGA_JTAG_TDI: R1011.2, U1001.K5
/fpga_core/FPGA_JTAG_TDO: R1013.2, U1001.L5
/fpga_core/FPGA_JTAG_TMS: R1012.2, U1001.M1
/fpga_core/FPGA_LOCAL_RESET_N: R1020.2, R1021.1, U1001.P1, U1003.4
/fpga_core/FPGA_SERVICE_RUN_N: R1016.2, U1003.2, U1005.2
/fpga_core/FPGA_USER_RESET_DELAYED: U1004.4, U1005.1
/fpga_core/FPGA_USER_RESET_RC: C1039.1, R1022.2, U1004.2
/mc_local_power/CORE_1V2_EN: R2002.1, R2102.2, R2103.1, U2001.5
/mc_local_power/CORE_1V2_MODE: R2001.1, U2001.7
/mc_local_power/CORE_1V2_OV_SENSE: R2051.2, R2055.1, U2004.15
/mc_local_power/CORE_1V2_SS: C2003.1, U2001.8
/mc_local_power/CORE_1V2_SW: L2001.1, U2001.2
/mc_local_power/CORE_1V2_UV_SENSE: R2042.2, R2047.1, U2004.16
/mc_local_power/CORE_5V: C2001.1, C2004.1, C2007.1, C2008.1, C2009.1, R2021.1, R2029.1, R2101.1, R2104.1, R2106.1, U2001.6, U2002.6, U2003.1, U2003.2, U2003.4, U2003.10, U2003.13, U2003.14, U2004.1, U2004.4, U2004.10, U2004.13, U2004.14, U2005.1, U2005.4, U2005.10, U2005.13, U2005.14
/mc_local_power/CORE_5V_OV_SENSE: R2029.2, R2035.1, U2003.15
/mc_local_power/CORE_5V_UV_SENSE: R2021.2, R2027.1, U2003.16
/mc_local_power/IO_3V3_EN: R2006.1, R2104.2, R2105.1, U2002.5, U2004.12, U2005.2
/mc_local_power/IO_3V3_MODE: R2005.1, U2002.7
/mc_local_power/IO_3V3_OV_SENSE: R2069.2, R2075.1, U2005.15
/mc_local_power/IO_3V3_SS: C2006.1, U2002.8
/mc_local_power/IO_3V3_SW: L2002.1, U2002.2
/mc_local_power/IO_3V3_UV_SENSE: R2061.2, R2067.1, U2005.16
/mc_local_power/IO_3V3_VSET: R2008.1, U2002.9
/mc_local_power/MC_RAILS_OK_5V: R2106.2, R2107.1, U2005.12, U2006.2
/mc_local_power/MC_SEQ_5V_OK: R2101.2, R2102.1, U2003.12, U2004.2
/mc_local_power/MC_SEQ_OV2_1: R2049.2, R2050.1
/mc_local_power/MC_SEQ_OV2_2: R2050.2, R2051.1
/mc_local_power/MC_SEQ_REF1: U2003.5, U2003.6, U2003.8, U2003.9
/mc_local_power/MC_SEQ_REF2: U2004.5, U2004.6, U2004.8, U2004.9
/mc_local_power/MC_SEQ_REF3: U2005.5, U2005.6, U2005.8, U2005.9
/mc_local_power/MC_SEQ_UV2_1: R2041.2, R2042.1
/mc_permission/ARM_M_Q: U4005.5, U4007.1
/mc_permission/ARM_O_Q: U4006.5, U4008.1
/mc_permission/BANK_B_BUFFER_ENABLE_QUALIFIED: R4014.1, U4013.6
/mc_permission/BASE_FIRST: U4001.4, U4002.1
/mc_permission/BASE_OK: U4002.4, U4003.1, U4004.1, U4009.1
/mc_permission/DIC_OK_QUALIFIED: R4010.1, U4001.6
/mc_permission/EXT_PERMIT_3V3: R4011.1, U4002.3
/mc_permission/LATCH_CLEAR_M_N: U4003.3, U4005.6
/mc_permission/LATCH_CLEAR_O_N: U4004.4, U4006.6
/mc_permission/OPI_REARM_BOE: R4004.1, U4013.1
/mc_permission/OPI_REARM_OUT: R4003.1, U4012.1
/mc_permission/OPI_REARM_TX: R4002.1, U4011.1
/mc_permission/OUTPUT_RAW_OK: U4008.6, U4009.7
/mc_permission/OUT_PERMIT: R4016.1, U4008.4, U4010.3, U4012.6
/mc_permission/PERMIT_OUT_DRIVE: R4018.1, U4009.3
/mc_permission/PERMIT_OUT_REQ: R4007.1, U4009.6
/mc_permission/PROCESS_PERMIT_EXT_3V3: R4013.1, U4010.6
/mc_permission/PROC_PERMIT: R4017.1, U4010.4
/mc_permission/TAMPER_CLEAR_N: R4012.1, U4002.6
/mc_permission/WD_M_FALL_CLK: U4014.1, U4016.6
/mc_permission/WD_M_RECORD_CLEAR_N: U4018.6, U4019.2
/mc_permission/WD_M_TRIP_CLEAR_N: U4014.6, U4019.7
/mc_permission/WD_M_TRIP_D: U4014.2, U4017.7
/mc_permission/WD_M_TRIP_Q: U4014.5, U4017.1
/mc_permission/WD_O_FALL_CLK: U4015.1, U4016.4
/mc_permission/WD_O_RECORD_CLEAR_N: U4018.4, U4019.6
/mc_permission/WD_O_TRIP_CLEAR_N: U4015.6, U4019.3
/mc_permission/WD_O_TRIP_D: U4015.2, U4017.3
/mc_permission/WD_O_TRIP_Q: U4015.5, U4017.5
/mc_permission/WD_REARM_M: R4005.1, U4018.1
/mc_permission/WD_REARM_O: R4006.1, U4018.3
/watchdog_conditioning/FPGA_PROGRESS_O: R3007.1, U3004.2
/watchdog_conditioning/WD_M_CWD: C3001.1, U3001.2
/watchdog_conditioning/WD_M_HEALTH_RAW: R3001.2, U3001.7, U3001.8, U3005.1
/watchdog_conditioning/WD_M_WDI_BUF: R3006.1, U3001.6, U3003.4
/watchdog_conditioning/WD_O_CWD: C3002.1, U3002.2
/watchdog_conditioning/WD_O_HEALTH_RAW: R3002.2, U3002.7, U3002.8, U3005.3
/watchdog_conditioning/WD_O_WDI_BUF: R3008.1, U3002.6, U3004.4
